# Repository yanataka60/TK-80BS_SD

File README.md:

# NEC TK-80BSにSD-Cardとのロード、セーブ機能

　ARDUINO+SD-CARDをTK-80BSに接続することでNEC TK-80BS LEVEL2 BASICでSD-CARDとロード、セーブを実現するものです。(LEVEL1 BASICは未所有のため対応していません。)

　実現するためにTK-80BS MONITOR、BS MONITOR及びLEVEL2 BASUCへのパッチ当て、SDアクセスルーチンを合わせてROMに焼く必要があります。

　パッチを当てたROMを使うのでTK-80のROM D454(D464)×3個、TK-80BSのBS MONITOR 2個、LEVEL2BASIC 1個はすべて引き抜きます。

　EXT-BOARD上のSRAM 62256により、A000h～CFFFhまでのRAMが増設されます。また、GAL22V10へ書き込むプログラムを選択することで8000h～81FFhのRAMを増設することも可能です。

　9800h～9FFFhのRAMはTK-80BSボード上で増設してください。

　TK-80標準装備のRAM D5101-E×4個(8200h～83FFh)は7SegLEDをDMA表示する為に必要ですので引き抜いてはいけません。(SRAM 62256では代わりになりません。)

## 回路図
　KiCadフォルダ内のTK-80_EXT-BOARD.pdfを参照してください。

　ROMとRAMの状況によりGAL22V10への書込みプログラムが変わります。

[回路図](https://github.com/yanataka60/TK-80BS_SD/blob/main/KiCad/TK-80_EXT-BOARD.pdf)

|番号|品名|数量|備考|
| ------------ | ------------ | ------------ | ------------ |
||J1、J2のいずれか|||
|J1|Micro_SD_Card_Kit|1|秋月電子通商 AE-microSD-LLCNV (注1)|
|J2|MicroSD Card Adapter|1|Arduino等に使われる5V電源に対応したもの(注2)|
|U1|8080A|1|TK-80から引き抜いたもの|
|U3|8228|1|TK-80から引き抜いたもの|
|U8|8255|1|TK-80から引き抜いたもの|
|U5|GAL22V10|1||
|U6|ROM 27512|1||
|U7|SRAM 62256|1||
|U10|Arduino_Pro_Mini_5V|1|Atmega328版を使用 168版は不可。(注3)|
|U2、U4、U9|Pin Header|40Pin×4、14Pin×2|秋月電子通商 細ピンヘッダーPHA-1x40SG又は基板用リードフレームBQ04-SN(注4)|
|C1-C3|積層セラミックコンデンサ 0.1uF|3||
|S1-S3|ピンヘッダ3Pin|3|秋月電子通商 ピンヘッダーPH-1x40SGなど|
|LS1|小型スピーカー|1|秋月電子通商 マイクロスピーカー又は圧電スピーカーPT08-Z185Rなど|
||ピンソケット(任意)|12Pin×2|Arduino_Pro_Miniを取り外し可能としたい場合に調達します 秋月電子通商 FHU-1x42SGなど|

### 注1)秋月電子通商　AE-microSD-LLCNVのJ1ジャンパはショートしてください。

### 注2)MicroSD Card Adapterを使う場合

J2に取り付けます。

MicroSD Card Adapterについているピンヘッダを除去してハンダ付けするのが一番確実ですが、J2の穴にMicroSD Card Adapterをぴったりと押しつけ、裏から多めにハンダを流し込むことでハンダ付けをする方法もあります。なお、この方法の時にはしっかりハンダ付けが出来たかテスターで導通を確認しておいた方が安心です。

ハンダ付けに自信のない方はJ1の秋月電子通商　AE-microSD-LLCNVをお使いください。AE-microSD-LLCNVならパワーLED、アクセスLEDが付いています。

### 注3)TK-80BS_SD(TK-80_SD)ではArduino Pro MiniのA4、A5ピンは使用しません。

### 注4)8080Aは左側、8228と8255は上側がピンヘッダーです。基板表面に各ICのICソケットをハンダ付けする前に基板裏面からピンヘッダーを挿し、基板表面でハンダ付けします。

細ピンヘッダーと基板用リードフレームのどちらを選択しても大丈夫ですが、あえて言うなら

〇細ピンヘッダー

　ピンが固く曲がってしまうことは無いので嵌めるときに位置合わせだけ気を付ければ大丈夫。

　細ピンとはいえピンに厚みがあるので嵌めるのに結構力が必要です。ちゃんと嵌っていないと外れやすいです。

　リードフレームより外し易いです。(簡単に抜けてしまうわけではないです)

　扱いがリードフレームより楽です。

〇リードフレーム

　ピンがすぐ曲がってしまうため、嵌めるときに気を付けないとピンが折れ曲がってしまう危険があります。

　嵌ってしまうとかなり外し難いです。無理に外そうとするとピンが曲がってしまうため慎重に外す必要があります。

　外れ難いということは、使っている分には外れないという安心感があります。

## ROMへの書込み
　まず、MONITOR-ROM(0000h-02FFh)、BS MONITOR-ROM(F000h-FFFFh)、LEVEL2 BASIC-ROM(D000h-EFFFh)の内容をすべて読み出し、それぞれのアドレスに配置して0000h～FFFFhまでのバイナリファイルを作成し、バイナリエディタ等で以下の修正をします。

|ADDRESS|修正前|修正後|
| ------------ | ------------ | ------------ |
|003C|FF|F0|
|0052|FF|F0|
|0080|D5 00|00 03|
|0082|07 01|03 03|
|024B|EF|E0|
|0258|DF|D0|
|0265|BF|B0|
|E2C6|4C 4F 41 44 48|46 49 4C 45 53|
|E42C|4B E5|0603|
|E42E|EE E4|0903|
|E430|FC E4|0603|
|E432|E1 E4|0C03|
|F1F7|43 54|5344|
|F1FB|A2 F2|0F03|
|F21F|F1 F2|1203|
|F225|4D F3|1503|

　次にバイナリエディタでTK-80BS_SDリポジトリ8080フォルダ中のfile_trans_TK80BS.binの内容で0300h～0977hを書き換えます。

　ROMに焼き、EXT-BOARDに装着します。

　ROMは27512を使うのでS1、S2、S3のショートピンは、全て左側を選択します。

## Arduinoへの書込み
　Arduino IDEを使ってArduinoフォルダTK-80_SDフォルダ内TK-80_SD.inoを書き込みます。

　SdFatライブラリを使用しているのでArduino IDEメニューのライブラリの管理からライブラリマネージャを立ち上げて「SdFat」をインストールしてください。

　「SdFat」で検索すれば見つかります。「SdFat」と「SdFat - Adafruit Fork」が見つかりますが「SdFat」のほうを使っています。

注)Arduinoを基板に直付けしている場合、Arduinoプログラムを書き込むときは、EXT-BOARDをTK-80本体から外し、GAL22V10を外したうえで書き込んでください。

## GAL22V10への書込み
　WINCUPLファルダに二通りのプログラムがあります。増設RAMの状況によりjedファイルを選択してROMライター(TL866II Plus等)を使ってGAL22V10に書き込んでください。

　(1)TK-80本体の増設RAM(8000h-81FFh)及びTK-80BSの増設RAM(9800h-9FFFh)を増設済みの場合

　TK80BS_1(ROM 0000-7BFF D000-FFFF,RAM A000-CFFF)フォルダのTK80.jed

　(2)TK-80本体の増設RAM(8000h-81FFh)は未装着、TK-80BSの増設RAM(9800h-9FFFh)は増設済みの場合

　TK80BS_2(ROM 0000-7BFF D000-FFFF,RAM 8000-81FF A000-CFFF)フォルダのTK80.jed

## SD-CARD
　出来れば8GB以下のSDカードを用意してください。

　ArduinoのSdFatライブラリは、SD規格(最大2GB)、SDHC規格(2GB～32GB)に対応していますが、SDXC規格(32GB～2TB)には対応していません。

　また、SDHC規格のSDカードであっても32GB、16GBは相性により動作しないものがあるようです。

　FAT16又はFAT32が認識できます。NTFSは認識できません。

## 操作方法
### TK-80
#### 扱えるファイル
　拡張子btkとなっているバイナリファイルです。

　ファイル名は0000～FFFFまでの16進数4桁を付けてください。(例:1000.btk)

　この16進数4桁がTK-80からSD-Card内のファイルを識別するファイルNoとなります。

　BTKファイルのフォーマットは、バイナリファイル本体データの先頭に開始アドレス、終了アドレスの4Byteのを付加した形になっています。

　パソコンのクロスアセンブラ等でTK-80用の実行binファイルを作成したらバイナリエディタ等で先頭に開始アドレス、終了アドレスの4Byteを付加し、ファイル名を変更したものをSD-Cardのルートディレクトリに保存すればTK-80から呼び出せるようになります。

#### Save
　4桁のファイルNo(xxxx)をデータ表示部のLEDに入力してSTORE DATAを押します。

　正常にSaveが完了するとアドレス部にスタートアドレス、データ部にエンドアドレスが表示されます。

　　　8000H～8390Hまでをxxxx.BTKとしてセーブします。セーブ範囲は固定となっていて指定はできません。

　「F0F0F0F0」と表示された場合はSD-Card未挿入です。確認してください。

#### Load
　4桁のファイルNo(xxxx)をデータ表示部のLEDに入力してLOAD DATAキーを押します。

　　　xxxx.BTKをBTKヘッダ情報で示されたアドレスにロードします。ただし、8391H～83FFHまでの範囲はライトプロテクトされます。

　正常にLoadが完了するとアドレス部にスタートアドレス、データ部にエンドアドレスが表示されます。スタートアドレスが実行開始アドレスであればそのままRUNキーを押すことでプログラムが実行できます。

　「F0F0F0F0F0」と表示された場合はSD-Card未挿入、「F1F1F1F1F1」と表示された場合はファイルNoのファイルが存在しない場合です。確認してください。

　異常が無いと思われるのにエラーとなってしまう場合にはTK-80をリセットしてからやり直してみてください。

### TK-80BSで扱えるファイル
　BS MONITOR、BS LEVEL2 BASIC共にルートに置かれた拡張子が「.CAS」ファイルのみ認識できます。(以外のファイル、フォルダも表示されますがLOAD実行の対象になりません)

　ファイル名は拡張子を除いて32文字まで、ただし半角カタカナ、及び一部の記号はArduinoが認識しないので使えません。パソコンでファイル名を付けるときはアルファベット、数字および空白でファイル名をつけてください。

　TK-80BSでのCASファイルとは、インテルHEX形式のファイルです。BIN2HEX等の変換プログラムでHEXファイルを作成した場合には拡張子をHEXからCASに変更して使ってください。

### TK-80BS MONITOR
#### SD[復改]又はSD,文字列[復改]
　文字列を入力せずにSD[復改]のみ入力するとSD-CARDルートディレクトリにあるファイルの一覧を表示します。

　文字列を付けて入力すればSD-CARDルートディレクトリにあるその文字列から始まるファイルの一覧を表示します。

　10件表示したところで指示待ちになるので打ち切るなら!を入力、Bキーで前の10件に戻ります。それ以外のキーで次の10件を表示します。

　行頭に0から9の数字を付加して表示してあるのでロードしたいファイルの頭についている数字を入力するとロードが実行されます。

　BASICプログラム、機械語プログラムのどちらもロード対象となり、8802hから始まるCASファイルがBASICプログラムとして認識され、それ以外のアドレスから始まるCASファイルは機械語プログラムとして認識します。

　BASICプログラムと認識した場合にはBASICテキスト終了ポインタもセットされます。

　表示される順番は、登録順となりファイル名アルファベッド順などのソートした順で表示することはできません。

##### 例)
　　SD[復改]

　　SD,SPACE[復改]

#### LT,DOSファイル名[復改]
　指定したDOSファイル名のファイルをSD-CARDからLOADします。

　拡張子「CAS」は入力してもしなくても構いません。

　BASICプログラム、機械語プログラムのどちらもロード対象となり、8802hから始まるCASファイルがBASICプログラムとして認識され、それ以外のアドレスから始まるCASファイルは機械語プログラムとして認識します。

　BASICプログラムと認識した場合にはBASICテキスト終了ポインタもセットされます。

##### 例)
　　LT,SPACE[復改]

#### LT[復改]
　複数のCASファイルを連結してまとめて一つのCASファイルとなっている場合、SDコマンド又はLT,DOSファイル名[復改]で一つ目のプログラムをロードしていた場合に限り二つ目以降のプログラムはLT[復改]のみでロード出来ます。

　複数のCASファイルの連結については後述します。

　BASICプログラム、機械語プログラムのどちらもロード対象となり、8802hから始まるCASファイルがBASICプログラムとして認識され、それ以外のアドレスから始まるCASファイルは機械語プログラムとして認識します。

　BASICプログラムと認識した場合にはBASICテキスト終了ポインタもセットされます。

#### ST,開始アドレス,終了アドレス,DOSファイル名[復改]
　開始アドレスから終了アドレスまでの機械語プログラムをDOSファイル名でSAVEします。

　拡張子「CAS」は自動的に付加されます。

##### 例)
　　ST,9000,93FF,SPACE[復改]

### TK-80BS LEVEL2 BASIC
#### FILES[復改]又はFILES 文字列[復改]
　文字列を入力せずにFILES[復改]のみ入力するとSD-CARDルートディレクトリにあるファイルの一覧を表示します。

　文字列を付けて入力すればSD-CARDルートディレクトリにあるその文字列から始まるファイルの一覧を表示します。

　文字列はダブルコーテーションで括っても括らなくてもどちらでも構いません。

　10件表示したところで指示待ちになるので打ち切るなら!を入力、Bキーで前の10件に戻ります。それ以外のキーで次の10件を表示します。

　行頭に0から9の数字を付加して表示してあるのでロードしたいファイルの頭についている数字を入力するとロードが実行されます。

　BASICプログラム、機械語プログラムのどちらもロード対象となり、8802hから始まるCASファイルがBASICプログラムとして認識され、それ以外のアドレスから始まるCASファイルは機械語プログラムとして認識します。

　BASICプログラムと認識した場合にはBASICテキスト終了ポインタもセットされます。

　表示される順番は、登録順となりファイル名アルファベッド順などのソートした順で表示することはできません。

##### 例)
　　FILES[復改]

　　FILES SPACE[復改]

　　FILES "SPACE"[復改]

#### LOAD DOSファイル名[復改]
#### LOADH DOSファイル名[復改]
　指定したDOSファイル名のファイルをSD-CARDからLOADします。

　LOADとLOADHは同じ動作をします。

　拡張子「CAS」は入力してもしなくても構いません。

　DOSファイル名はダブルコーテーションで括っても括らなくてもどちらでも構いません。

　BASICプログラム、機械語プログラムのどちらもロード対象となり、8802hから始まるCASファイルがBASICプログラムとして認識され、それ以外のアドレスから始まるCASファイルは機械語プログラムとして認識します。

　BASICプログラムと認識した場合にはBASICテキスト終了ポインタもセットされます。

##### 例)
　　LOAD SPACE[復改]

　　LOAD "SPACE"[復改]

#### LOAD[復改]
#### LOADH[復改]
　複数のCASファイルを連結してまとめて一つのCASファイルとなっている場合、FILESコマンド又はLOAD DOSファイル名[復改]で一つ目のプログラムをロードしていた場合に限り二つ目以降のプログラムはLOAD[復改]のみでロード出来ます。

　LOADとLOADHは同じ動作をします。

　複数のCASファイルの連結については後述します。

　BASICプログラム、機械語プログラムのどちらもロード対象となり、8802hから始まるCASファイルがBASICプログラムとして認識され、それ以外のアドレスから始まるCASファイルは機械語プログラムとして認識します。

　BASICプログラムと認識した場合にはBASICテキスト終了ポインタもセットされます。

#### SAVE DOSファイル名[復改]
　BASICプログラムをDOSファイル名でSAVEします。SAVEHは使えません。

　拡張子「CAS」は自動的に付加されます。

　DOSファイル名はダブルコーテーションで括っても括らなくてもどちらでも構いません。

##### 例)
　　SAVE SPACE[復改]

　　SAVE "SPACE"[復改]

## CASファイルの連結
　BASICプログラムから機械語プログラムを呼び出して動くアプリケーションの場合、それぞれ別のDOSファイル名で保存して別々にLOADしても良いのですが、１本のCASファイルにまとめて扱うことも可能です。

　例えば「TESTBAS.CAS」と「TESTBIN.CAS」をまとめる場合にはテキストエディタで「TESTBAS.CAS」の後ろに「TESTBIN.CAS」をコピーし別名で保存します。例として「TESTBASBIN.CAS」とします。

「TESTBAS.CAS」

「TESTBIN.CAS」

「TESTBASBIN.CAS」

　このファイルは「LOAD TESTBASBIN[復改]」としてBASICプログラムをLOADし、次に「LOAD[復改]」とすることで機械語プログラムが読み込まれるCASファイルとなります。

　また、「TESTBAS.CAS」の最終行を削除してから「TESTBIN.CAS」をコピーし別名で保存すれば、「LOAD TESTBASBIN[復改]」でBASICプログラムと機械語プログラムをまとめてLOADすることも可能です。

　BASICプログラムと機械語プログラムの連結を例にあげましたが、BASICプログラムとBASICプログラム、機械語プログラムと機械語プログラムでも同じです。

　また、３つ以上のプログラムをまとめてしまうことも可能です。

## 追記
2024.11.30　Arduinoプログラムに安定性の向上を追加

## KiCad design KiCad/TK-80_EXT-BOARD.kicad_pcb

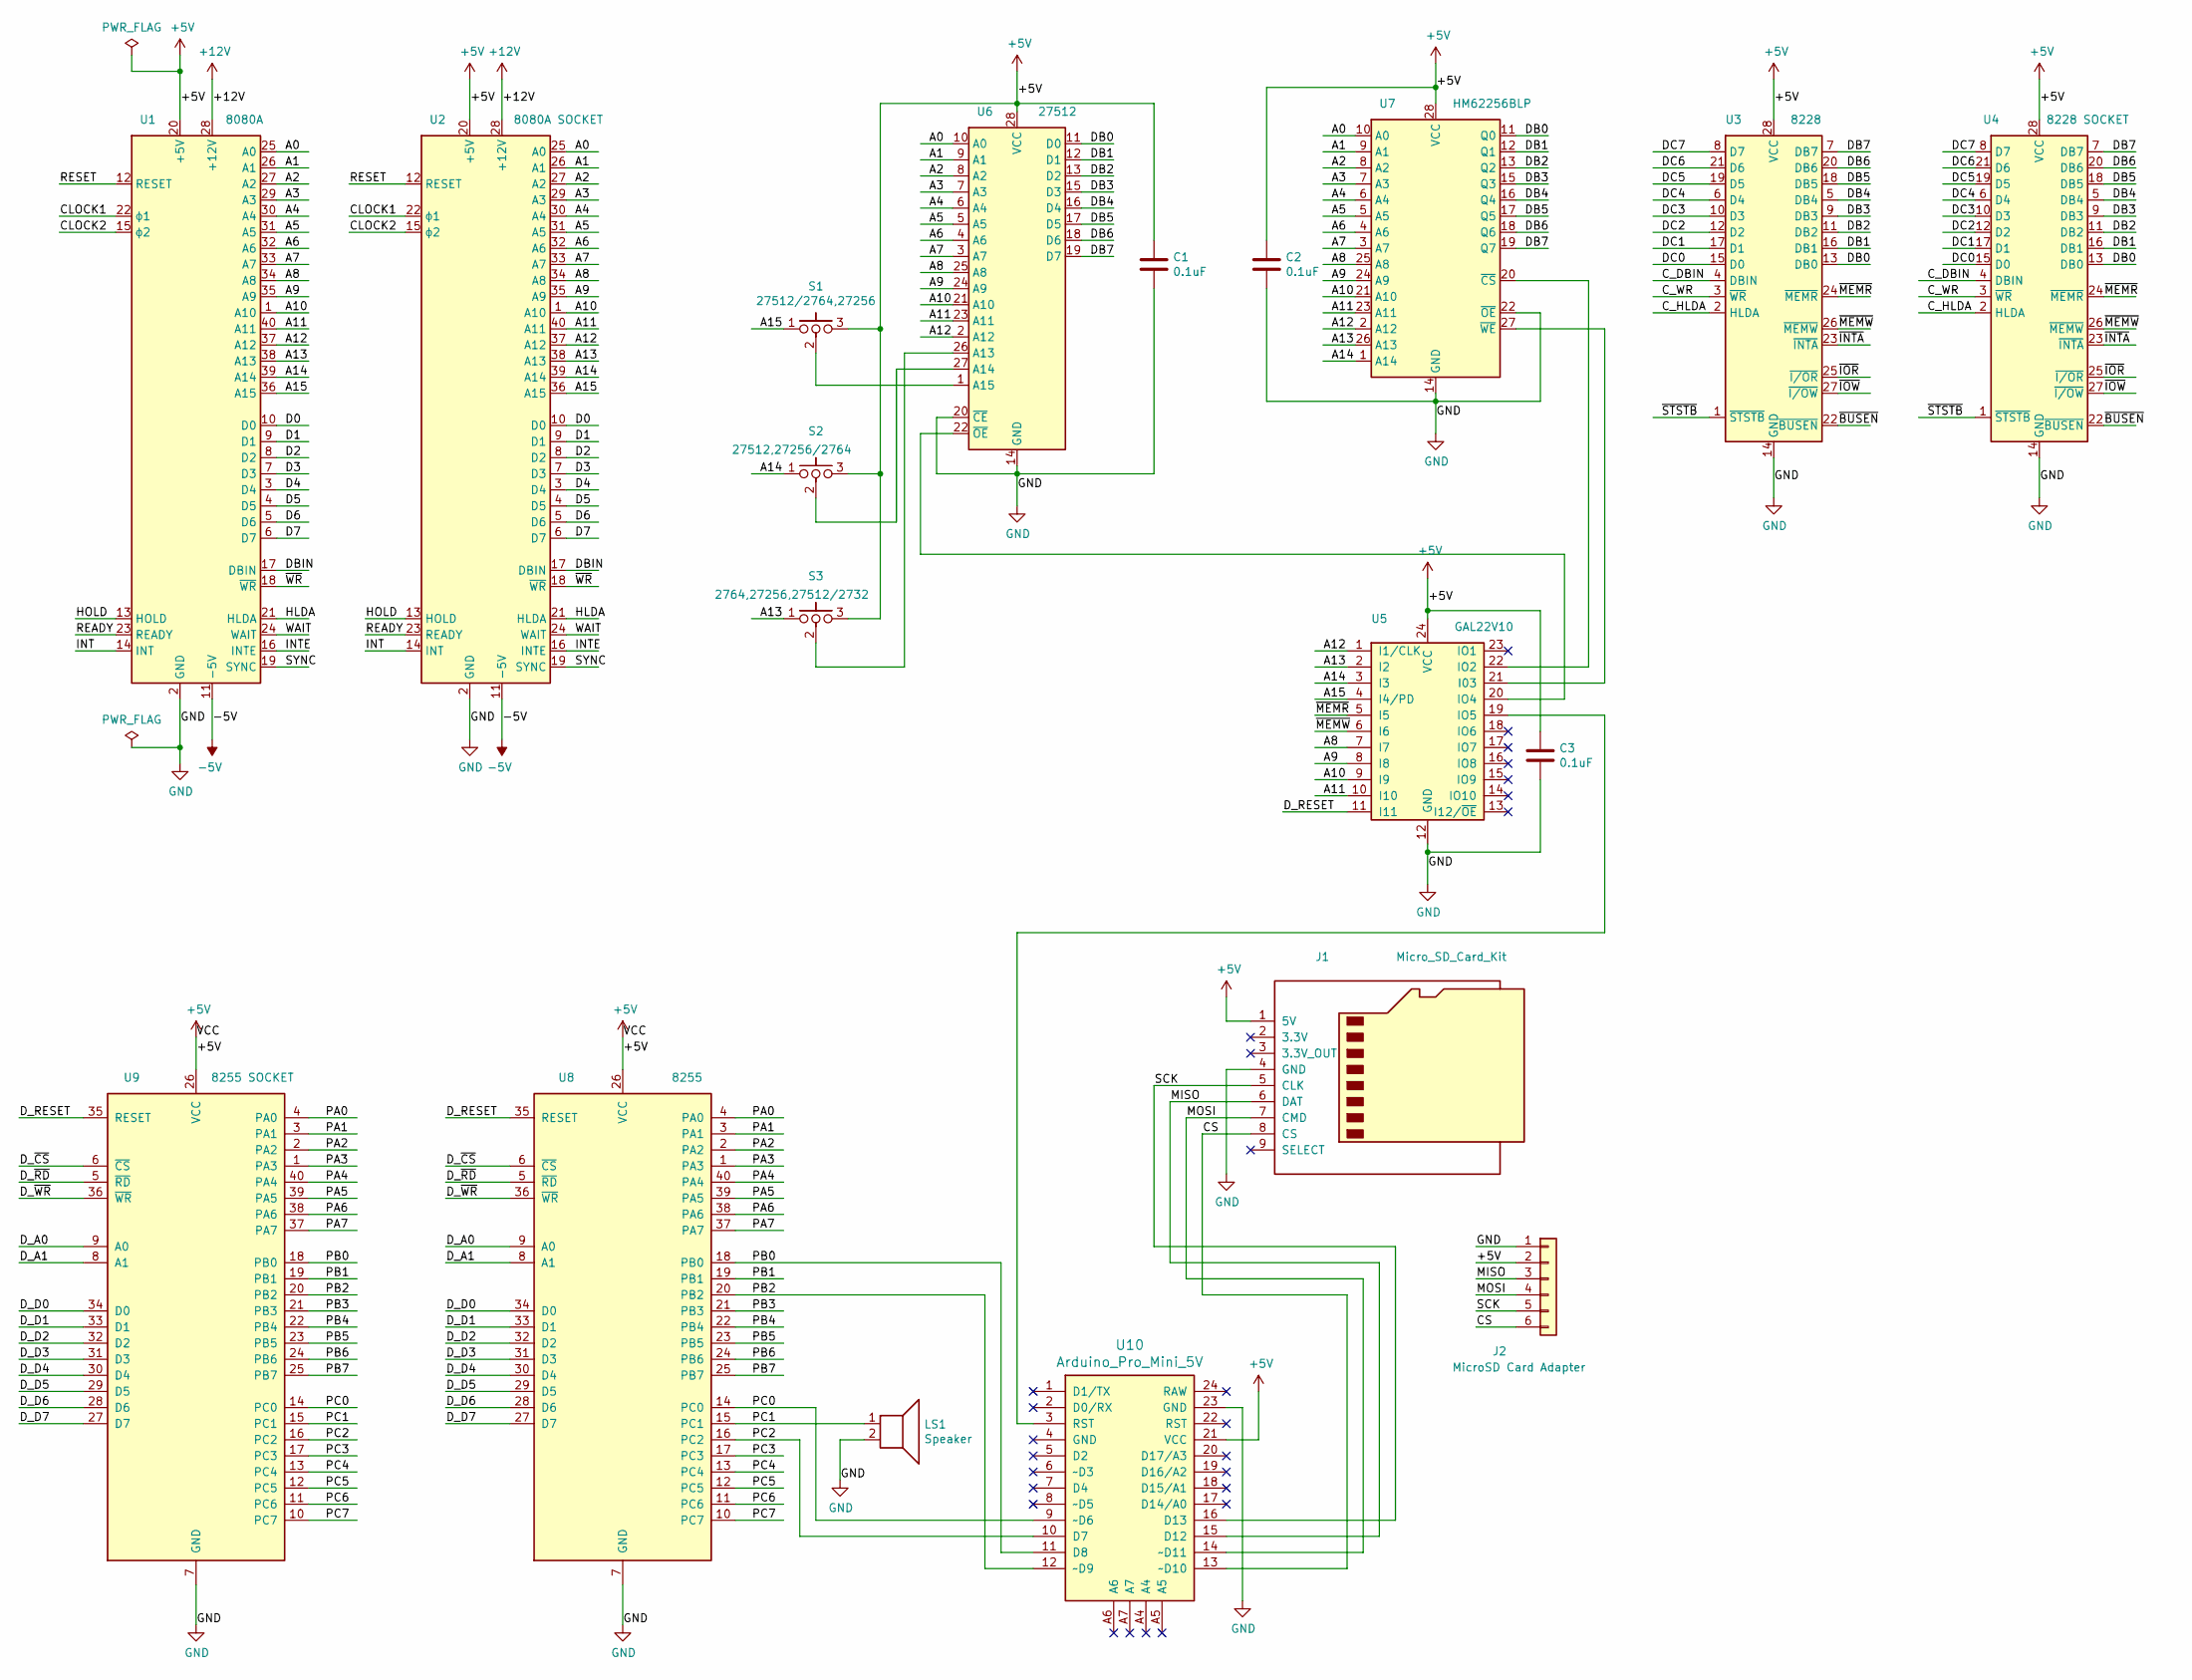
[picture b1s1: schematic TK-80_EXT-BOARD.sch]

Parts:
C1, C2, C3: 0.1uF; C_Rect_L4.0mm_W2.5mm_P2.50mm
J1: Micro_SD_Card_Kit; AE-microSD-LLCNV
J2: MicroSD Card Adapter; PinSocket_1x06_P2.54mm_Vertical
LS1: Speaker; PinHeader_1x02_P2.54mm_Vertical
S1: 27512/2764,27256; PinHeader_1x03_P2.54mm_Vertical
S2: 27512,27256/2764; PinHeader_1x03_P2.54mm_Vertical
S3: 2764,27256,27512/2732; PinHeader_1x03_P2.54mm_Vertical
U1: 8080A; DIP-40_W15.24mm_LongPads
U2: 8080A SOCKET; DIP-40_W15.24mm_LongPads
U3: 8228; DIP-28_W15.24mm_LongPads
U4: 8228 SOCKET; DIP-28_W15.24mm_LongPads
U5: GAL22V10; DIP-24_W7.62mm_LongPads
U6: 27512; DIP-28_W15.24mm_LongPads
U7: HM62256BLP; DIP-28_W15.24mm_LongPads
U8: 8255; DIP-40_W15.24mm_LongPads
U9: 8255 SOCKET; DIP-40_W15.24mm_LongPads
U10: Arduino_Pro_Mini_5V; Arduino_Pro_Mini

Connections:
+5V: C1.1, C2.1, C3.1, J1.1 (5V), J2.2, S1.3, S2.3, S3.3, U1.20 (+5V), U2.20 (+5V), U3.28 (VCC), U4.28 (VCC), U5.24 (VCC), U6.28 (VCC), U7.28 (VCC), U8.26 (VCC), U9.26 (VCC), U10.21 (VCC)
+12V: U1.28 (+12V), U2.28 (+12V)
-5V: U1.11 (-5V), U2.11 (-5V)
/A0: U1.25 (A0), U2.25 (A0), U6.10 (A0), U7.10 (A0)
/A1: U1.26 (A1), U2.26 (A1), U6.9 (A1), U7.9 (A1)
/A2: U1.27 (A2), U2.27 (A2), U6.8 (A2), U7.8 (A2)
/A3: U1.29 (A3), U2.29 (A3), U6.7 (A3), U7.7 (A3)
/A4: U1.30 (A4), U2.30 (A4), U6.6 (A4), U7.6 (A4)
/A5: U1.31 (A5), U2.31 (A5), U6.5 (A5), U7.5 (A5)
/A6: U1.32 (A6), U2.32 (A6), U6.4 (A6), U7.4 (A6)
/A7: U1.33 (A7), U2.33 (A7), U6.3 (A7), U7.3 (A7)
/A8: U1.34 (A8), U2.34 (A8), U5.7 (I7), U6.25 (A8), U7.25 (A8)
/A9: U1.35 (A9), U2.35 (A9), U5.8 (I8), U6.24 (A9), U7.24 (A9)
/A10: U1.1 (A10), U2.1 (A10), U5.9 (I9), U6.21 (A10), U7.21 (A10)
/A11: U1.40 (A11), U2.40 (A11), U5.10 (I10), U6.23 (A11), U7.23 (A11)
/A12: U1.37 (A12), U2.37 (A12), U5.1 (I1/CLK), U6.2 (A12), U7.2 (A12)
/A13: S3.1, U1.38 (A13), U2.38 (A13), U5.2 (I2), U7.26 (A13)
/A14: S2.1, U1.39 (A14), U2.39 (A14), U5.3 (I3), U7.1 (A14)
/A15: S1.1, U1.36 (A15), U2.36 (A15), U5.4 (I4/PD)
/CLOCK1: U1.22 (ϕ1), U2.22 (ϕ1)
/CLOCK2: U1.15 (ϕ2), U2.15 (ϕ2)
/CS: J1.8 (CS), J2.6, U10.13 (~~D10)
/C_DBIN: U3.4 (DBIN), U4.4 (DBIN)
/C_HLDA: U3.2 (HLDA), U4.2 (HLDA)
/C_WR: U3.3 (~WR), U4.3 (~WR)
/D0: U1.10 (D0), U2.10 (D0)
/D1: U1.9 (D1), U2.9 (D1)
/D2: U1.8 (D2), U2.8 (D2)
/D3: U1.7 (D3), U2.7 (D3)
/D4: U1.3 (D4), U2.3 (D4)
/D5: U1.4 (D5), U2.4 (D5)
/D6: U1.5 (D6), U2.5 (D6)
/D7: U1.6 (D7), U2.6 (D7)
/DB0: U3.13 (DB0), U4.13 (DB0), U6.11 (D0), U7.11 (Q0)
/DB1: U3.16 (DB1), U4.16 (DB1), U6.12 (D1), U7.12 (Q1)
/DB2: U3.11 (DB2), U4.11 (DB2), U6.13 (D2), U7.13 (Q2)
/DB3: U3.9 (DB3), U4.9 (DB3), U6.15 (D3), U7.15 (Q3)
/DB4: U3.5 (DB4), U4.5 (DB4), U6.16 (D4), U7.16 (Q4)
/DB5: U3.18 (DB5), U4.18 (DB5), U6.17 (D5), U7.17 (Q5)
/DB6: U3.20 (DB6), U4.20 (DB6), U6.18 (D6), U7.18 (Q6)
/DB7: U3.7 (DB7), U4.7 (DB7), U6.19 (D7), U7.19 (Q7)
/DBIN: U1.17 (DBIN), U2.17 (DBIN)
/DC0: U3.15 (D0), U4.15 (D0)
/DC1: U3.17 (D1), U4.17 (D1)
/DC2: U3.12 (D2), U4.12 (D2)
/DC3: U3.10 (D3), U4.10 (D3)
/DC4: U3.6 (D4), U4.6 (D4)
/DC5: U3.19 (D5), U4.19 (D5)
/DC6: U3.21 (D6), U4.21 (D6)
/DC7: U3.8 (D7), U4.8 (D7)
/D_A0: U8.9 (A0), U9.9 (A0)
/D_A1: U8.8 (A1), U9.8 (A1)
/D_D0: U8.34 (D0), U9.34 (D0)
/D_D1: U8.33 (D1), U9.33 (D1)
/D_D2: U8.32 (D2), U9.32 (D2)
/D_D3: U8.31 (D3), U9.31 (D3)
/D_D4: U8.30 (D4), U9.30 (D4)
/D_D5: U8.29 (D5), U9.29 (D5)
/D_D6: U8.28 (D6), U9.28 (D6)
/D_D7: U8.27 (D7), U9.27 (D7)
/D_RESET: U5.11 (I11), U8.35 (RESET), U9.35 (RESET)
/D_~CS: U8.6 (~CS~), U9.6 (~CS~)
/D_~RD: U8.5 (~RD~), U9.5 (~RD~)
/D_~WR: U8.36 (~WR~), U9.36 (~WR~)
/HLDA: U1.21 (HLDA), U2.21 (HLDA)
/HOLD: U1.13 (HOLD), U2.13 (HOLD)
/INT: U1.14 (INT), U2.14 (INT)
/INTE: U1.16 (INTE), U2.16 (INTE)
/MISO: J1.6 (DAT), J2.3, U10.15 (D12)
/MOSI: J1.7 (CMD), J2.4, U10.14 (~~D11)
/PA0: U8.4 (PA0), U9.4 (PA0)
/PA1: U8.3 (PA1), U9.3 (PA1)
/PA2: U8.2 (PA2), U9.2 (PA2)
/PA3: U8.1 (PA3), U9.1 (PA3)
/PA4: U8.40 (PA4), U9.40 (PA4)
/PA5: U8.39 (PA5), U9.39 (PA5)
/PA6: U8.38 (PA6), U9.38 (PA6)
/PA7: U8.37 (PA7), U9.37 (PA7)
/PB0: U8.18 (PB0), U9.18 (PB0), U10.11 (D8)
/PB1: U8.19 (PB1), U9.19 (PB1)
/PB2: U8.20 (PB2), U9.20 (PB2), U10.12 (~~D9)
/PB3: U8.21 (PB3), U9.21 (PB3)
/PB4: U8.22 (PB4), U9.22 (PB4)
/PB5: U8.23 (PB5), U9.23 (PB5)
/PB6: U8.24 (PB6), U9.24 (PB6)
/PB7: U8.25 (PB7), U9.25 (PB7)
/PC0: U8.14 (PC0), U9.14 (PC0), U10.9 (~~D6)
/PC1: LS1.1, U8.15 (PC1), U9.15 (PC1)
/PC2: U8.16 (PC2), U9.16 (PC2), U10.10 (D7)
/PC3: U8.17 (PC3), U9.17 (PC3)
/PC4: U8.13 (PC4), U9.13 (PC4)
/PC5: U8.12 (PC5), U9.12 (PC5)
/PC6: U8.11 (PC6), U9.11 (PC6)
/PC7: U8.10 (PC7), U9.10 (PC7)
/READY: U1.23 (READY), U2.23 (READY)
/RESET: U1.12 (RESET), U2.12 (RESET)
/SCK: J1.5 (CLK), J2.5, U10.16 (D13)
/SYNC: U1.19 (SYNC), U2.19 (SYNC)
/WAIT: U1.24 (WAIT), U2.24 (WAIT)
/~BUSEN: U3.22 (~BUSEN), U4.22 (~BUSEN)
/~INTA: U3.23 (~INTA), U4.23 (~INTA)
/~IOR: U3.25 (~I/OR), U4.25 (~I/OR)
/~IOW: U3.27 (~I/OW), U4.27 (~I/OW)
/~MEMR: U3.24 (~MEMR), U4.24 (~MEMR), U5.5 (I5)
/~MEMW: U3.26 (~MEMW), U4.26 (~MEMW), U5.6 (I6)
/~STSTB: U3.1 (~STSTB), U4.1 (~STSTB)
/~WR: U1.18 (~WR~), U2.18 (~WR~)
GND: C1.2, C2.2, C3.2, J1.4 (GND), J2.1, LS1.2, U1.2 (GND), U2.2 (GND), U3.14 (GND), U4.14 (GND), U5.12 (GND), U6.14 (GND), U6.20 (~CE), U7.14 (GND), U7.22 (~OE), U8.7 (GND), U9.7 (GND), U10.23 (GND)
unnamed: S1.2, U6.1 (A15)
unnamed: S2.2, U6.27 (A14)
unnamed: S3.2, U6.26 (A13)
unnamed: U5.20 (IO4), U6.22 (~OE)
unnamed: U5.21 (I03), U7.27 (~WE)
unnamed: U5.22 (IO2), U7.20 (~CS)
unnamed: U5.19 (IO5), U10.3 (RST)

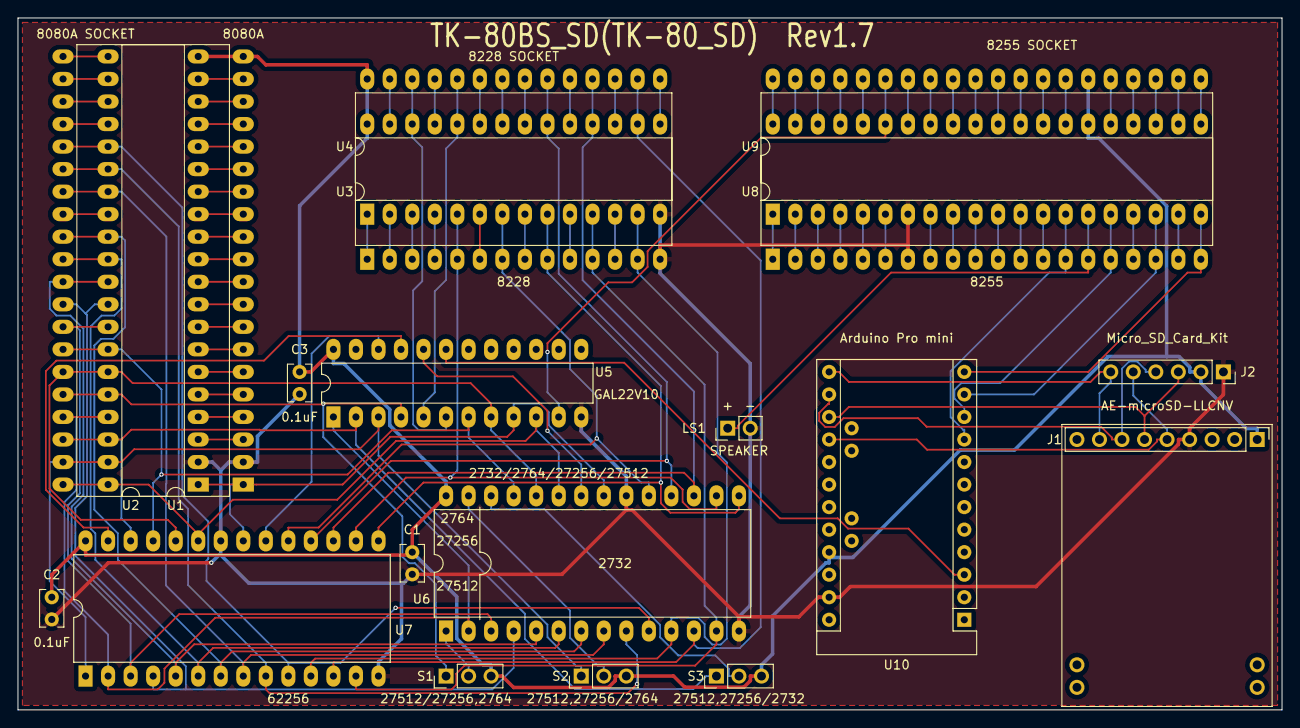
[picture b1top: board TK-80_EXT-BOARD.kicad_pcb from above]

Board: 2 copper layers, 142.5 x 78.0 mm, 19 parts (0 on the bottom side), 115 nets.
